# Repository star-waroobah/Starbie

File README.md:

# Starbie

A small star-shaped PCB desk pet built around a XIAO ESP32-C3, with an OLED screen, a motion sensor and a temperature sensor.

## Why I made it
I made it as the week 1 project of half life hack club and I picked Starbie because it’s a small, fun project that combines a screen, sensors and buttons on one board. It was a great way to learn KiCad as a beginner using the guide :)

## How it works
The XIAO ESP32-C3 is the brain. It draws the pet on the OLED screen, reads the MPU6050 so the pet reacts when the board is tilted or shaken, reads the DHT11 for temperature and humidity, and reads two buttons for input.

## How the parts fit together
- **XIAO ESP32-C3 (U1):** the microcontroller. It powers everything from its 3V3 pin and GND.
- **OLED display (J1, 4-pin header):** pin 1 GND, pin 2 3.3V, pin 3 SCL (D5), pin 4 SDA (D4)
- **MPU6050 module (J2, 8-pin header):** pin 1 3.3V, pin 2 GND, pin 3 SCL (D5), pin 4 SDA (D4). It shares the I2C lines with the OLED. Pins 5 to 8 are unused.
- **DHT11 (U2):** data pin to D1. A 10k pull-up resistor (R1) connects the data line to 3.3V.
- **Button 1 (SW1):** connects D2 to GND
- **Button 2 (SW2):** connects D3 to GND
  
## Firmware Credits
The firmware used in this project is based on the original Starbie firmware provided by SharKingStudios in the Hack Club Half-Life guide.
Original firmware: https://github.com/SharKingStudios/Starbie/tree/main/Firmware
The original firmware is licensed under the MIT License, Copyright (c) 2026 Logan Peterson. The license text is included in this repository.
I followed the official guide for the firmware rather than generating it with AI.

## Bill of Materials (BOM)

| Part | What it does | Qty | Unit price | Total | Vendor | Link |
|------|--------------|-----|-----------|-------|--------|------|
| XIAO ESP32-C3 | The main chip | 1 | $4.90 | $4.90 | Seeed Studio | [Buy](https://www.seeedstudio.com/Seeed-XIAO-ESP32C3-p-5431.html) |
| 0.96 inch OLED display (I2C) | Screen that shows the pet | 1 | $3.76 | $3.76 | Daraz | [Buy](https://tinyurl.com/9mjyudrn) |
| DHT11 | Temperature and humidity sensor | 1 | $2.90 | $2.90 | Daraz | [Buy](https://tinyurl.com/9fm7tvjk) |
| 10k resistor (pack of 10) | Pull-up resistor on the DHT11 data line | 1 | $0.42 | $0.42 | Daraz | [Buy](https://www.daraz.pk//products/i465392816-s2198965661.html?spm=a2o42.cart.0.0.22717d68aTIudk&urlFlag=true) |
| Custom PCB (Starbie) | The circuit board, made from my Gerber files | 1 | $6.44 | $6.44 | PCBX | [Buy](https://www.pcbx.com/order/manufacturing/pcb) |
| MPU6050 module | Motion sensor that detects tilting and shaking | 1 | $1.81 | $1.81 | Daraz | [Buy](https://tinyurl.com/fe83xnmz) |
| Tactile push buttons 6x6x5mm | The 2 buttons on the board | 1 | $1.08 | $1.08 | Daraz | [Buy](https://tinyurl.com/4ehe2pe8) |
| Tax & shipping | For the whole order | - | - | $7.40 | - | - |
| **Total** | | | | **$28.71** | | |
  
## Schematic

## PCB layout

## 3D model

## Repo files
- `PCB/` KiCad project files
- `production/` Gerber and drill files
- `Firmware/` Arduino code
- `Assets/` images
- `BOM.csv` parts list

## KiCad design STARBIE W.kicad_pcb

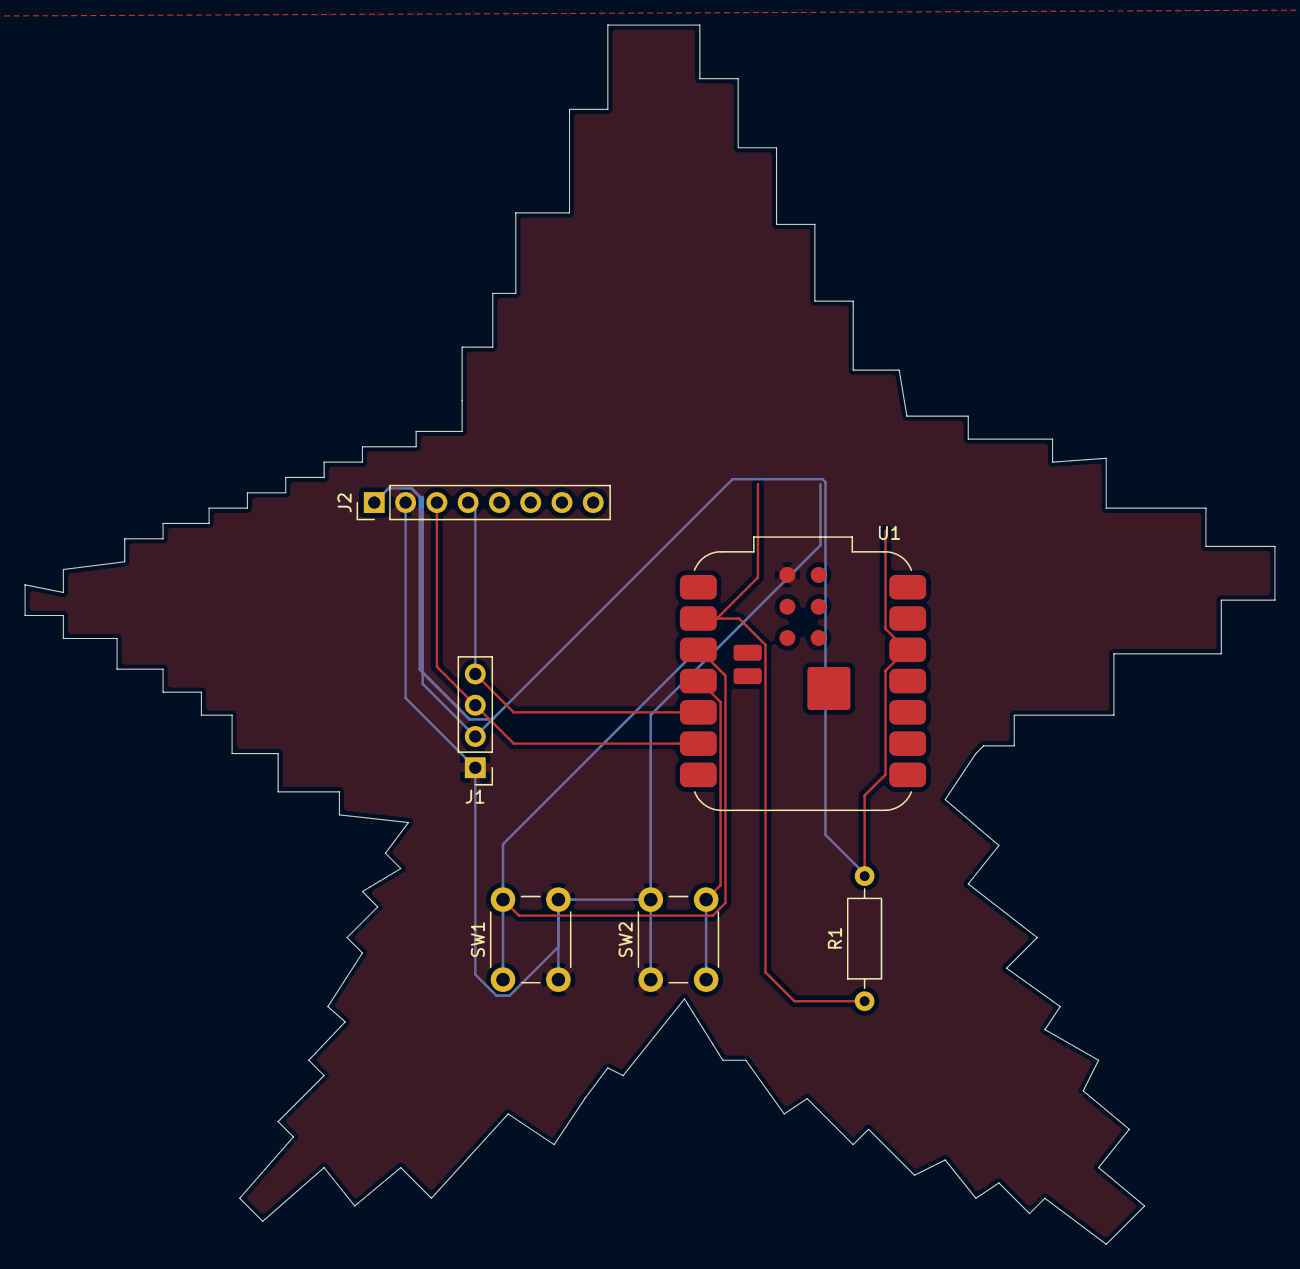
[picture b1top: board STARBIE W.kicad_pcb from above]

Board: 2 copper layers, 101.5 x 99.0 mm, 6 parts (0 on the bottom side), 7 nets.

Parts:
J1: Conn_01x04; PinHeader_1x04_P2.54mm_Vertical
J2: Conn_01x08; PinHeader_1x08_P2.54mm_Vertical
R1: 10k; R_Axial_DIN0207_L6.3mm_D2.5mm_P10.16mm_Horizontal
SW1, SW2: SW_Push; SW_PUSH_6mm
U1: XIAO-ESP32-C3-SMD; MCU_Seeed_ESP32C3

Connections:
+3.3V: J1.2, J2.1, R1.2, U1.12 (3V3_OUT)
/BTN1: SW1.1, U1.3 (D2)
/BTN2: SW2.2, U1.4 (D3)
/DHT: R1.1, U1.2 (D1)
/SCL: J1.3, J2.3, U1.6 (D5)
/SDA: J1.4, J2.4, U1.5 (D4)
GND: J1.1, J2.2, SW1.2, SW2.1, U1.18 (GND)
